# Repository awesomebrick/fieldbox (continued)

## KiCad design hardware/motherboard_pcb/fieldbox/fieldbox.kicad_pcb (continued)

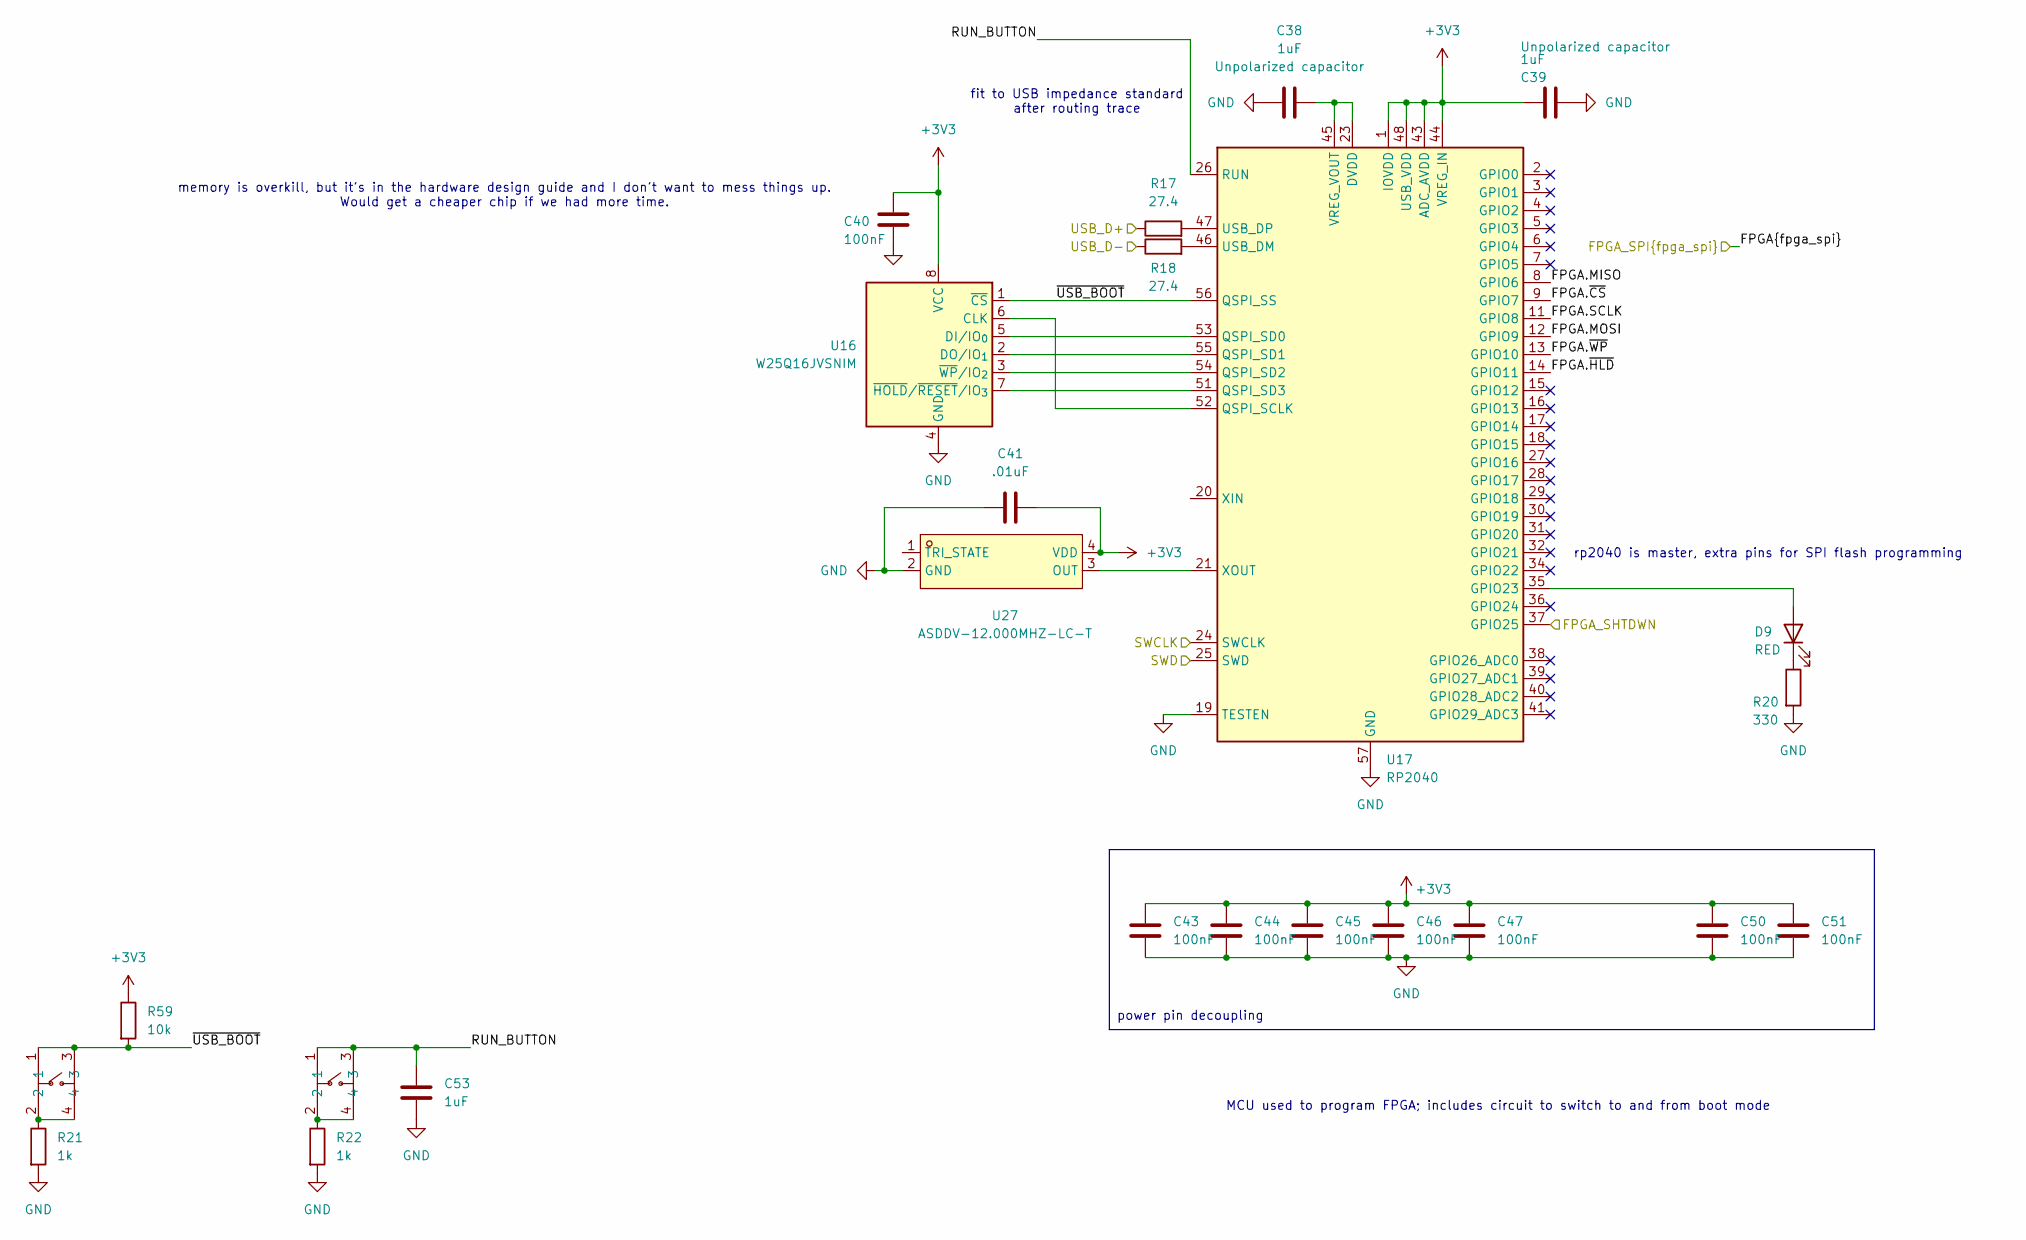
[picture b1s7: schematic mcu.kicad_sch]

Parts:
C38, C39, C53: 1uF; C_0603_1608Metric; Mouser # 791-0201X105M6R3CT
C40, C43, C44, C45, C46, C47, C50, C51: 100nF; C_0603_1608Metric; Mouser # KGM15AR71C104MM
C41: .01uF; C_0603_1608Metric; Mouser # 603-CC603ZRY5V8BB103
D9: RED; LED_0603_1608Metric; Mouser # 720-LSQ976.01-N1Q2-1
R17, R18: 27.4; R_0603_1608Metric; Mouser # 603-RC0603FR-0727R4L
R20: 330; R_0603_1608Metric; Mouser # 603-RC0603FR-10330RL
R21, R22: 1k; R_0603_1608Metric; Mouser # 660-RK73H1JTTDD1001F
R59: 10k; R_0603_1608Metric; Mouser # 652-CRT0603BY1002ELF
U16: W25Q16JVSNIM; SOIC-8_5.3x5.3mm_P1.27mm; Mouser # 454-W25Q16JVSNIM
U17: RP2040; QFN-56-1EP_7x7mm_P0.4mm_EP3.2x3.2mm; Mouser # 358-SC091413
U27: ASDDV-12.000MHZ-LC-T; OSC-SMD_4P-L2.5-W2.0-BL_ABRACON_ASTMLPD; Mouser # 815-ASDDV-1200MHZLCT; LCSC Part C1857773
b_up1, b_up2: TSD003A04126A02; SW-SMD_4P-L6.0-W6.0-P4.50-LS8.6; Mouser # NA; LCSC Part C2888573

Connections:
+3V3: C39.1, C40.1, C41.2, C43.1, C44.1, C45.1, C46.1, C47.1, C50.1, C51.1, R59.1, U16.8 (VCC), U17.1 (IOVDD), U17.10 (IOVDD), U17.22 (IOVDD), U17.33 (IOVDD), U17.42 (IOVDD), U17.43 (ADC_AVDD), U17.44 (VREG_IN), U17.48 (USB_VDD), U17.49 (IOVDD), U27.4 (VDD); also elsewhere on the board
/CV inputs/FPGA_SHTDWN: U17.37 (GPIO25); also elsewhere on the board
/FPGA/SPI_MASTER.MISO: U17.8 (GPIO6); also elsewhere on the board
/FPGA/SPI_MASTER.MOSI: U17.12 (GPIO9); also elsewhere on the board
/FPGA/SPI_MASTER.SCLK: U17.11 (GPIO8); also elsewhere on the board
/FPGA/SPI_MASTER.~CS: U17.9 (GPIO7); also elsewhere on the board
/FPGA/SPI_MASTER.~HLD: U17.14 (GPIO11); also elsewhere on the board
/FPGA/SPI_MASTER.~WP: U17.13 (GPIO10); also elsewhere on the board
/USB_D+: R17.1; also elsewhere on the board
/USB_D-: R18.1; also elsewhere on the board
/mcu/RUN_BUTTON: C53.1, U17.26 (RUN), b_up2.1, b_up2.3
/mcu/SWCLK: U17.24 (SWCLK); also elsewhere on the board
/mcu/SWD: U17.25 (SWD); also elsewhere on the board
/mcu/~USB_BOOT: R59.2, U16.1 (~CS), U17.56 (QSPI_SS), b_up1.1, b_up1.3
GND: C38.2, C39.2, C40.2, C41.1, C43.2, C44.2, C45.2, C46.2, C47.2, C50.2, C51.2, C53.2, R20.2, R21.2, R22.2, U16.4 (GND), U17.19 (TESTEN), U17.57 (GND), U27.2 (GND); also elsewhere on the board
unnamed: D9.2 (A), U17.35 (GPIO23)
unnamed: D9.1 (K), R20.1
unnamed: R21.1, b_up1.2, b_up1.4
unnamed: R22.1, b_up2.2, b_up2.4
unnamed: U16.6 (CLK), U17.52 (QSPI_SCLK)
unnamed: U16.5 (DI/IO_{0}), U17.53 (QSPI_SD0)
unnamed: U16.2 (DO/IO_{1}), U17.55 (QSPI_SD1)
unnamed: U16.7 (~HOLD/~RESET/IO_{3}), U17.51 (QSPI_SD3)
unnamed: U16.3 (~WP/IO_{2}), U17.54 (QSPI_SD2)
unnamed: R18.2, U17.46 (USB_DM)
unnamed: R17.2, U17.47 (USB_DP)
unnamed: C38.1, U17.23 (DVDD), U17.45 (VREG_VOUT), U17.50 (DVDD)
unnamed: U17.21 (XOUT), U27.3 (OUT)

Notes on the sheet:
power pin decoupling
MCU used to program FPGA; includes circuit to switch to and from boot mode
rp2040 is master, extra pins for SPI flash programming
fit to USB impedance standard after routing trace
memory is overkill, but it's in the hardware design guide and I don't want to mess things up. Would get a cheaper chip if we had more time.

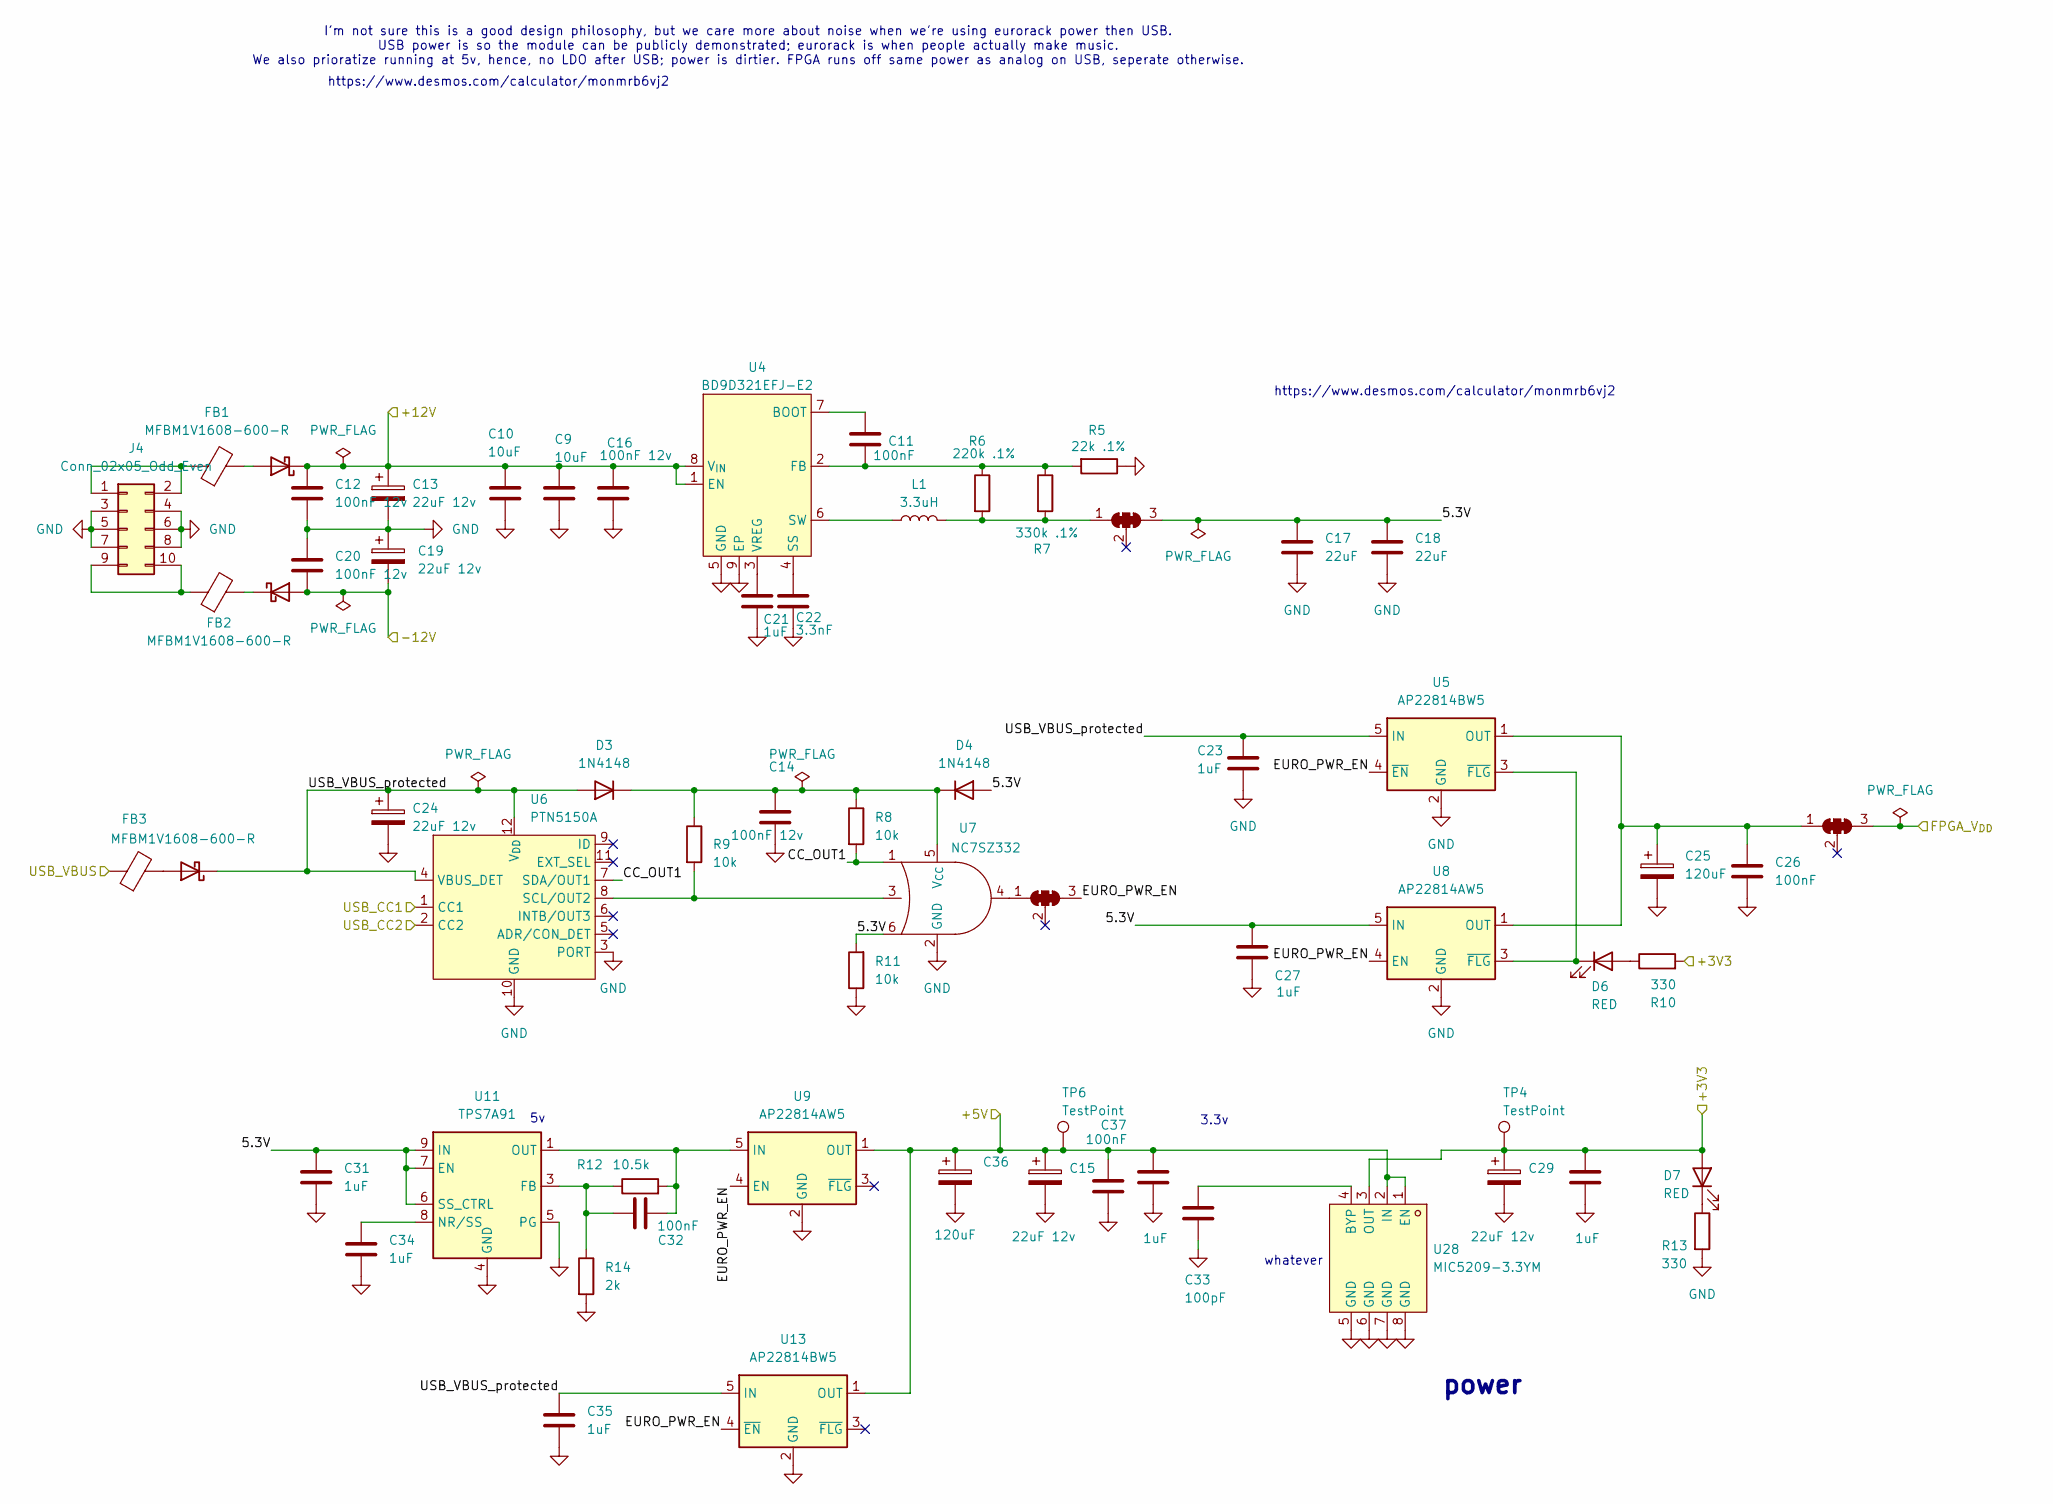
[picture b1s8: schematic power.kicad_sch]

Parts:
C9, C10: 10uF; CP_EIA-3216-18_Kemet-A; Mouser # 581-TAJA106K016R
C11, C26, C32, C37: 100nF; C_0603_1608Metric; Mouser # KGM15AR71C104MM
C12, C14, C16, C20: 100nF 12v; C_0603_1608Metric; Mouser # KGM15AR71C104MM
C13, C15, C19, C24, C29: 22uF 12v; CP_EIA-3528-21_Kemet-B; Mouser # 581-TAJB226K016TNJ
C17, C18: 22uF; C_0603_1608Metric; Mouser # 81-GRM188R60J226ME5J
C21, C23, C27, C28, C30, C31, C34, C35: 1uF; C_0603_1608Metric; Mouser # 791-0201X105M6R3CT
C22: 3.3nF; C_0603_1608Metric; Mouser # CL10B332KB8NFNC
C25, C36: 120uF; CP_EIA-3528-21_Kemet-B; Mouser # 581-TPSB107M006R0400
C33: 100pF; C_0603_1608Metric; Mouser # 603-CC603KRX7R8BB101
D1: SK34SMA-3G; D_SMA; Mouser # 637-SK34SMA-3G
D2, D5: SK34SMA-3G; D_SMA; mfr # SK34SMA-3G; Mouser # 637-SK34SMA-3G
D3, D4: 1N4148; D_SOD-323F; Mouser # 637-1N4148WS-AQ
D6, D7: RED; LED_0603_1608Metric; Mouser # 720-LSQ976.01-N1Q2-1
FB1, FB2, FB3: MFBM1V1608-600-R; L_0603_1608Metric; Mouser # 704-MFBM1V1608-600-R
J4: Conn_02x05_Odd_Even; IDC-Header_2x05_P2.54mm_Vertical; Mouser # 737-BHR-10-VUA
JP1, JP2, JP3: SolderJumper_3_Bridged123; SolderJumper-3_P2.0mm_Open_TrianglePad1.0x1.5mm
L1: 3.3uH; L_APV_ANR4012; Mouser # 963-NRS4012T3R3MDGJ
R5: 22k .1%; R_0603_1608Metric; Mouser # 754-RG1608P-223-B-T5
R6: 220k .1%; R_0603_1608Metric; Mouser # 754-RG1608P-224-BT5
R7: 330k .1%; R_0603_1608Metric; Mouser # 754-RG1608P-334-B-T5
R8, R9, R11: 10k; R_0603_1608Metric; Mouser # 652-CRT0603BY1002ELF
R10, R13: 330; R_0603_1608Metric; Mouser # 603-RC0603FR-10330RL
R12: 10.5k; R_0603_1608Metric; Mouser # 667-ERA-3AEB1052V
R14: 2k; R_0603_1608Metric; Mouser # 660-RN73H1JTD2001B25
TP4, TP6: TestPoint; TestPoint_Pad_2.0x2.0mm; Mouser # NA
U4: BD9D321EFJ-E2; HTSOP-8-1EP_3.9x4.9mm_P1.27mm_EP2.4x3.2mm; Mouser # 755-BD9D321EFJ-E2
U5, U13: AP22814BW5; SOT-23-5; Mouser # 621-AP22814BW5-7
U6: PTN5150A; Texas_X2QFN-12_1.6x1.6mm_P0.4mm; Mouser # 771-PTN5150AHXMP
U7: NC7SZ332; SOT-363_SC-70-6; Mouser # 512-NC7SZ332P6X
U8, U9: AP22814AW5; SOT-23-5; Mouser # 621-AP22814AW5-7
U11: TPS7A91; SON50P250X250X80-11N-D; Mouser # 595-TPS7A9101DSKR
U28: MIC5209-3.3YM; SOIC-8_L4.9-W3.9-P1.27-LS6.0-BL; Mouser # MIC5209-3.3YM

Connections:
+3V3: C29.1, C30.1, D7.2 (A), R10.2, TP4.1, U28.3 (OUT); also elsewhere on the board
+5V: C15.1, C28.1, C36.1, C37.1, TP6.1, U9.1 (OUT), U13.1 (OUT), U28.1 (EN), U28.2 (IN); also elsewhere on the board
+12V: C9.1, C10.1, C12.2, C13.1, C16.1, D1.1 (K), U4.1 (EN), U4.8 (V_{IN}); also elsewhere on the board
-12V: C19.2, C20.1, D2.2 (A); also elsewhere on the board
/FPGA/FPGA_VDD: JP2.3 (B); also elsewhere on the board
/USB_CC1: U6.1 (CC1); also elsewhere on the board
/USB_CC2: U6.2 (CC2); also elsewhere on the board
/USB_VBUS: FB3.1; also elsewhere on the board
/power/5.3V: C17.1, C18.1, C27.1, C31.1, D4.2 (A), JP1.3 (B), R11.2, U7.6, U8.5 (IN), U11.6 (SS_CTRL), U11.7 (EN), U11.9 (IN), U11.10 (IN)
/power/CC_OUT1: R8.2, U6.7 (SDA/OUT1), U7.1
/power/EURO_PWR_EN: JP3.3 (B), U5.4 (~EN), U8.4 (EN), U9.4 (EN), U13.4 (~EN)
/power/USB_VBUS_protected: C23.1, C24.1, C35.1, D3.2 (A), D5.1 (K), U5.5 (IN), U6.4 (VBUS_DET), U6.12 (V_{DD}), U13.5 (IN)
GND: C9.2, C10.2, C12.1, C13.2, C14.2, C15.2, C16.2, C17.2, C18.2, C19.1, C20.2, C21.2, C22.2, C23.2, C24.2, C25.2, C26.2, C27.2, C28.2, C29.2, C30.2, C31.2, C33.2, C34.2, C35.2, C36.2, C37.2, J4.3, J4.4, J4.5, J4.6, J4.7, J4.8, R5.1, R11.1, R13.2, R14.2, U4.5 (GND), U4.9 (EP), U5.2 (GND), U6.3 (PORT), U6.10 (GND), U7.2 (GND), U8.2 (GND), U9.2 (GND), U11.4 (GND), U11.5 (PG), U11.11 (GND), U13.2 (GND), U28.5 (GND), U28.6 (GND), U28.7 (GND), U28.8 (GND); also elsewhere on the board
unnamed: D1.2 (A), FB1.2
unnamed: D2.1 (K), FB2.2
unnamed: C14.1, D3.1 (K), D4.1 (K), R8.1, R9.1, U7.5 (V_{CC})
unnamed: D5.2 (A), FB3.2
unnamed: D6.2 (A), R10.1
unnamed: D6.1 (K), U5.3 (~FLG), U8.3 (~FLG)
unnamed: D7.1 (K), R13.1
unnamed: FB1.1, J4.1, J4.2
unnamed: FB2.1, J4.9, J4.10
unnamed: JP1.1 (A), L1.2, R6.2, R7.2
unnamed: C25.1, C26.1, JP2.1 (A), U5.1 (OUT), U8.1 (OUT)
unnamed: JP3.1 (A), U7.4
unnamed: C11.2, U4.7 (BOOT)
unnamed: C11.1, R5.2, R6.1, R7.1, U4.2 (FB)
unnamed: C22.1, U4.4 (SS)
unnamed: L1.1, U4.6 (SW)
unnamed: C21.1, U4.3 (VREG)
unnamed: R9.2, U6.8 (SCL/OUT2), U7.3
unnamed: C32.1, R12.2, U9.5 (IN), U11.1 (OUT), U11.2 (OUT)
unnamed: C32.2, R12.1, R14.1, U11.3 (FB)
unnamed: C34.1, U11.8 (NR/SS)
unnamed: C33.1, U28.4 (BYP)

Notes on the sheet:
3.3v
power
whatever
https://www.desmos.com/calculator/monmrb6vj2
I'm not sure this is a good design philosophy, but we care more about noise when we're using eurorack power then USB. USB power is so the module can be publicly demonstrated; eurorack is when people actually make music. We also prioratize running at 5v, hence, no LDO after USB; power is dirtier. FP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

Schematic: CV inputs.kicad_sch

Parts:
C54, C55, C56, C57: 100nF; C_0603_1608Metric; Mouser # KGM15AR71C104MM
C58: 10uF; CP_EIA-3216-18_Kemet-A; Mouser # 581-TAJA106K016R
C59: 100nF; C_0603_1608Metric; Mouser # KGM15AR71C104MM; not fitted
D10, D11, D12, D13, D15, D16, D18, D19: 1N4148; D_SOD-323F; Mouser # 637-1N4148WS-AQ
JP4: Jumper_2_Open; R_0603_1608Metric
R23, R24, R31, R32, R40, R41, R51, R52: 33k; R_0603_1608Metric; Mouser # CR0603-FX-3302ELF
R25: 10k .1%; R_0603_1608Metric; Mouser # 652-CRT0603BY1002ELF
R26, R28, R30, R33, R36, R37, R44, R45, R48, R53, R54, R55: 100k; R_0603_1608Metric; Mouser # CR0603-FX-1003ELF
R27, R29: 20k .1%; R_0603_1608Metric; Mouser # 708-RNCF0603BTC20K0
U1, U18, U21: TL074; TSSOP-14_4.4x5mm_P0.65mm; Mouser # 595-TL074HIPWR
U10: 74LVC1G32; SOT-353_SC-70-5; Mouser # 771-74LVC1G32GW-G
U20: MCP3462R; TSSOP-20_4.4x6.5mm_P0.65mm; Mouser # MCP3462R-E/ST

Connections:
+3V3: C54.2, C55.1, C56.2, C57.1, C58.1, C59.1, R27.1, U10.5 (VCC), U20.1 (AV_{DD}), U20.4 (RFIN+/OUT), U20.20 (DV_{DD}); also elsewhere on the board
+5V: D10.1 (K), D12.1 (K), D15.1 (K), D18.1 (K); also elsewhere on the board
+12V: U18.4 (V+), U21.4 (V+); also elsewhere on the board
-12V: U18.11 (V-), U21.11 (V-); also elsewhere on the board
/-5V_CUTOFF: D11.2 (A), D13.2 (A), D16.2 (A), D19.2 (A); also elsewhere on the board
/CV inputs/CV_ADC_MCLK: U20.18 (MCLK); also elsewhere on the board
/CV inputs/CV_REF: R23.1, R25.2, R31.1, R40.1, R51.1, U1.7
/CV inputs/FPGA_SHTDWN: U10.1; also elsewhere on the board
/CV inputs/RAW_SCALED_CV_1: JP4.2 (B); also elsewhere on the board
/CV inputs/SCALED_CV_1: JP4.1 (A), R24.2, U18.7, U20.5 (CH0)
/CV inputs/SCALED_CV_2: R32.2, U18.8, U20.6 (CH1)
/CV inputs/SCALED_CV_3: R41.2, U20.7 (CH2), U21.7
/CV inputs/SCALED_CV_4: R52.2, U20.8 (CH3), U21.8
/CV inputs/adc.MISO: U20.16 (SDO)
/CV inputs/adc.MOSI: U20.15 (SDI); also elsewhere on the board
/CV inputs/adc.SCLK: U20.14 (SCK); also elsewhere on the board
/CV inputs/adc.~IRQ: U20.17 (~IRQ/MDAT)
/CV inputs/adc.~SS: U10.2; also elsewhere on the board
/CV inputs/~SS: U10.4, U20.13 (~CS)
/EURORACK_CV_IN_1: R26.1; also elsewhere on the board
/EURORACK_CV_IN_2: R33.1; also elsewhere on the board
/EURORACK_CV_IN_3: R44.1; also elsewhere on the board
/EURORACK_CV_IN_4: R53.1; also elsewhere on the board
GND: C54.1, C55.2, C56.1, C57.2, C58.2, C59.2, R29.2, U1.5 (+), U10.3 (GND), U18.6 (-), U18.9 (-), U20.2 (A_{GND}), U20.3 (REFIN-), U20.19 (D_{GND}), U21.6 (-), U21.9 (-); also elsewhere on the board
unnamed: D10.2 (A), D11.1 (K), R26.2, U18.3 (+)
unnamed: D12.2 (A), D13.1 (K), R33.2, U18.12 (+)
unnamed: D15.2 (A), D16.1 (K), R44.2, U21.3 (+)
unnamed: D18.2 (A), D19.1 (K), R53.2, U21.12 (+)
unnamed: R28.1, R30.2, U18.1
unnamed: R36.1, R37.2, U18.14
unnamed: R45.1, R48.2, U21.1
unnamed: R54.1, R55.2, U21.14
unnamed: R25.1, R27.2, R29.1, U1.6 (-)
unnamed: R30.1, U18.2 (-)
unnamed: R23.2, R24.1, R28.2, U18.5 (+)
unnamed: R31.2, R32.1, R36.2, U18.10 (+)
unnamed: R37.1, U18.13 (-)
unnamed: R48.1, U21.2 (-)
unnamed: R40.2, R41.1, R45.2, U21.5 (+)
unnamed: R51.2, R52.1, R54.2, U21.10 (+)
unnamed: R55.1, U21.13 (-)

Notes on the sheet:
converts euro->CV ADC and contains CV ADC
<-- in case we don't get the external ADC working, we'll use the FPGA ADC
All these 10 ohm resistors are reccomended but probably useless in our case will remove if we're short on space
https://www.desmos.com/calculator/vk5jdnuxcy
CV inputs

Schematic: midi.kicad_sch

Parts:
D14, D17: 1N4148; D_SOD-323F; Mouser # 637-1N4148WS-AQ
R38, R47: 220; R_0603_1608Metric; Mouser # 652-CR0603FX-2200ELF
R39: 1k; R_0603_1608Metric; Mouser # 660-RK73H1JTTDD1001F
U19, U22: H11L1M; DIP-6_W7.62mm; Mouser # 512-H11L1M

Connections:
+3V3: R39.1, U19.6, U22.6; also elsewhere on the board
/FPGA/MIDI_IN: R39.2, U19.4, U22.4; also elsewhere on the board
/MIDI_IN_R: D17.2 (A), R38.1, U22.2; also elsewhere on the board
/MIDI_IN_S: D14.2 (A), R47.1, U19.2; also elsewhere on the board
GND: U19.5, U22.5; also elsewhere on the board
unnamed: D14.1 (K), R38.2, U19.1
unnamed: D17.1 (K), R47.2, U22.1

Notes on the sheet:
MIDI input

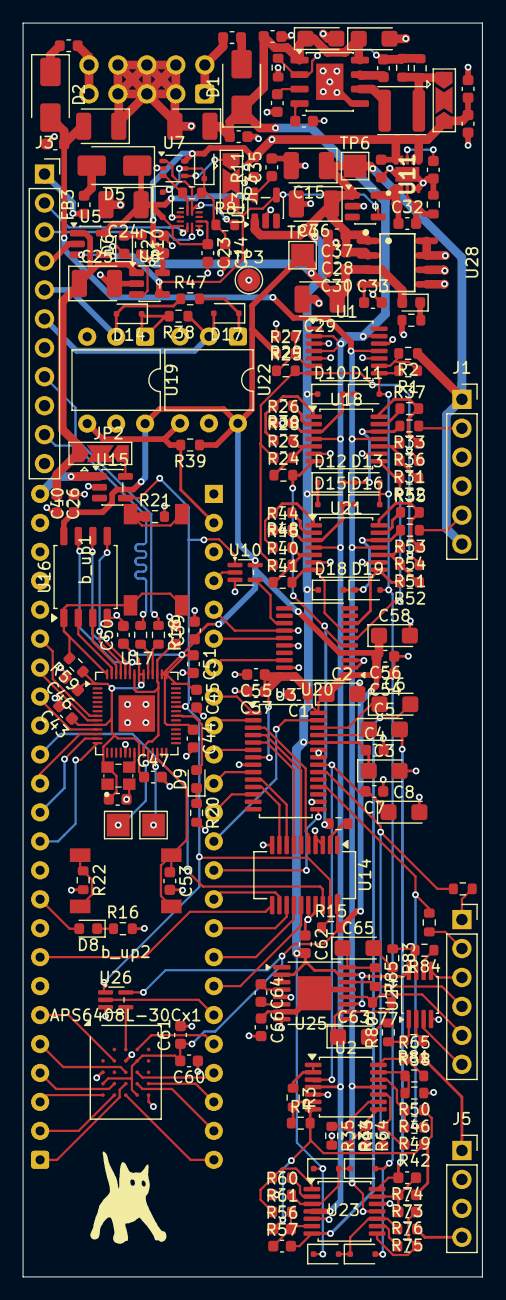
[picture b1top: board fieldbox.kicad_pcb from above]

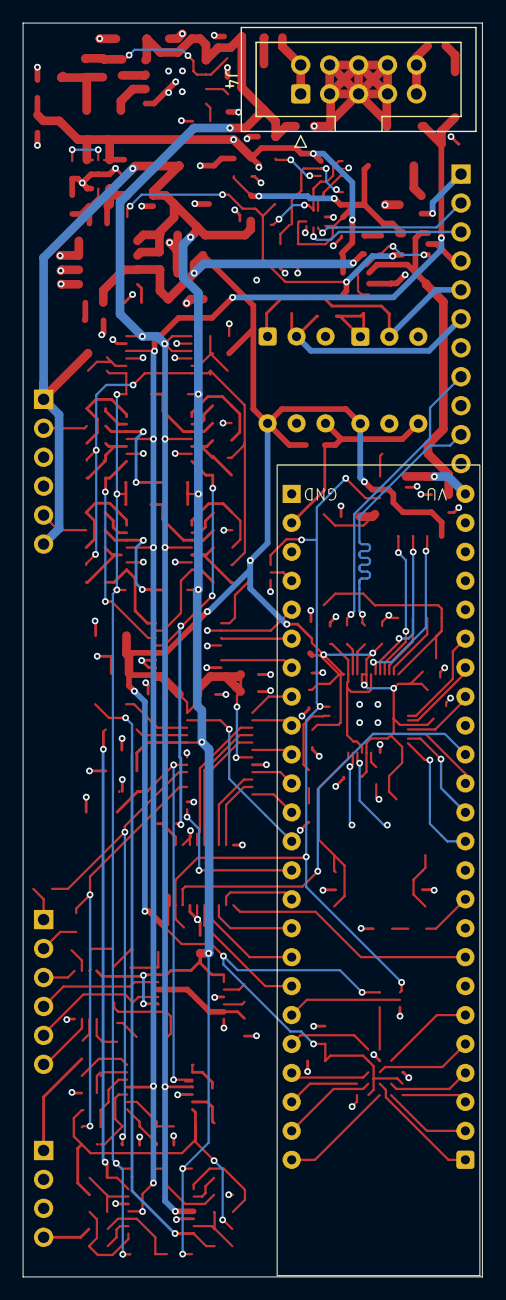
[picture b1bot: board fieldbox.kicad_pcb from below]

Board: 4 copper layers, 40.3 x 110.0 mm, 209 parts (2 on the bottom side), 179 nets.

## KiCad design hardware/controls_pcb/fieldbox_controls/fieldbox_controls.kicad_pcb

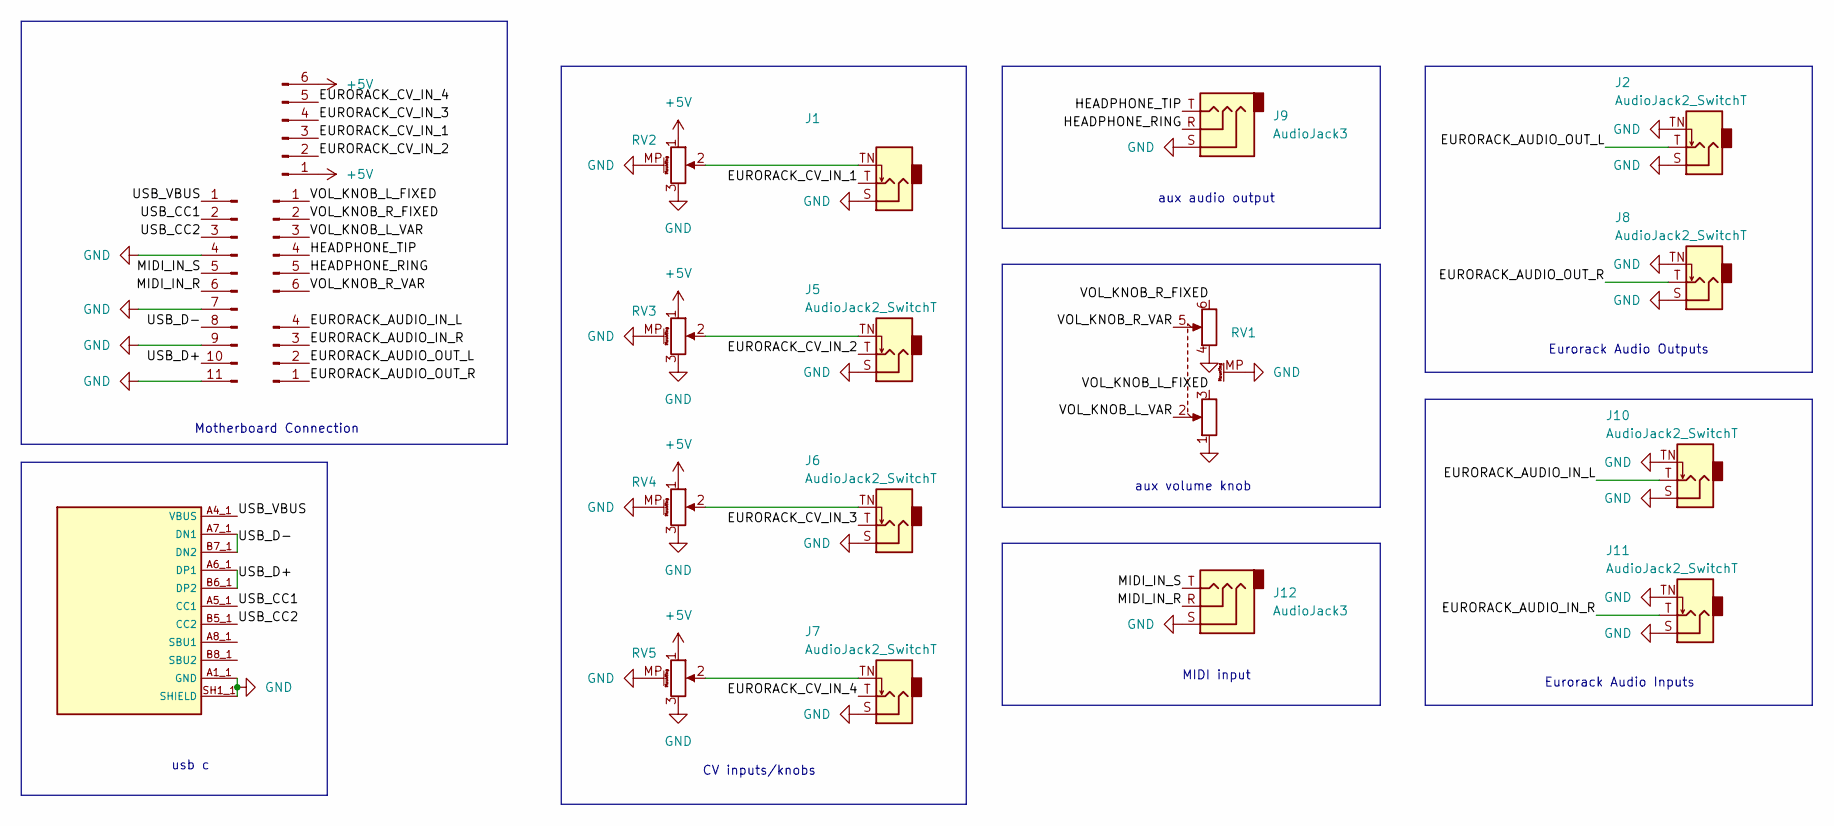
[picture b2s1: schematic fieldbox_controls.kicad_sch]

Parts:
J1, J2, J5, J6, J7, J8, J10, J11: AudioJack2_SwitchT; Jack_3.5mm_QingPu_WQP-PJ398SM_Vertical
J9, J12: AudioJack3; Jack_3.5mm_QingPu_WQP-PJ366ST_Vertical
J13: Conn_01x06_Socket; PinHeader_1x06_P2.54mm_Vertical
J14: Conn_01x04_Socket; PinHeader_1x06_P2.54mm_Vertical
J15: Conn_01x11_Socket; PinHeader_1x11_P2.54mm_Vertical
J16: Conn_01x04_Socket; PinHeader_1x04_P2.54mm_Vertical
RV1: R_Potentiometer_Dual_MountingPin; RK09L12D0A1W; Mouser # 688-RK09L12D0A1W
RV2, RV3, RV4, RV5: R_Potentiometer_MountingPin; RK09L114001E; Mouser # 688-RK09L114001T
U1: CUI_UJ20-C-V-C-3-SMT-TR; Mouser # 179-UJ20CVC3SMTTR

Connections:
+5V: J14.1, J14.6, RV2.1, RV3.1, RV4.1, RV5.1
/EURORACK_AUDIO_IN_L: J10.T, J16.4
/EURORACK_AUDIO_IN_R: J11.T, J16.3
/EURORACK_AUDIO_OUT_L: J2.T, J16.2
/EURORACK_AUDIO_OUT_R: J8.T, J16.1
/EURORACK_CV_IN_1: J1.T, J14.3
/EURORACK_CV_IN_2: J5.T, J14.2
/EURORACK_CV_IN_3: J6.T, J14.4
/EURORACK_CV_IN_4: J7.T, J14.5
/HEADPHONE_RING: J9.R, J13.5
/HEADPHONE_TIP: J9.T, J13.4
/MIDI_IN_R: J12.R, J15.6
/MIDI_IN_S: J12.T, J15.5
/USB_CC1: J15.2, U1.A5_1 (CC1), U1.A5_2 (CC1__1), U1.A5_3 (CC1__2), U1.A5_4 (CC1__3)
/USB_CC2: J15.3, U1.B5_1 (CC2), U1.B5_2 (CC2__1), U1.B5_3 (CC2__2), U1.B5_4 (CC2__3)
/USB_D+: J15.10, U1.A6_1 (DP1), U1.A6_2 (DP1__1), U1.A6_3 (DP1__2), U1.A6_4 (DP1__3), U1.B6_1 (DP2), U1.B6_2 (DP2__1), U1.B6_3 (DP2__2), U1.B6_4 (DP2__3)
/USB_D-: J15.8, U1.A7_1 (DN1), U1.A7_2 (DN1__1), U1.A7_3 (DN1__2), U1.A7_4 (DN1__3), U1.B7_1 (DN2), U1.B7_2 (DN2__1), U1.B7_3 (DN2__2), U1.B7_4 (DN2__3)
/USB_VBUS: J15.1, U1.A4_1 (VBUS), U1.A4_2 (VBUS__1), U1.A4_3 (VBUS__2), U1.A4_4 (VBUS__3), U1.A9_1 (VBUS__4), U1.A9_2 (VBUS__5), U1.A9_3 (VBUS__6), U1.A9_4 (VBUS__7), U1.B4_1 (VBUS__8), U1.B4_2 (VBUS__9), U1.B4_3 (VBUS__10), U1.B4_4 (VBUS__11), U1.B9_1 (VBUS__12), U1.B9_2 (VBUS__13), U1.B9_3 (VBUS__14), U1.B9_4 (VBUS__15)
/VOL_KNOB_L_FIXED: J13.1, RV1.3
/VOL_KNOB_L_VAR: J13.3, RV1.2
/VOL_KNOB_R_FIXED: J13.2, RV1.6
/VOL_KNOB_R_VAR: J13.6, RV1.5
GND: J1.S, J2.S, J2.TN, J5.S, J6.S, J7.S, J8.S, J8.TN, J9.S, J10.S, J10.TN, J11.S, J11.TN, J12.S, J15.4, J15.7, J15.9, J15.11, RV1.1, RV1.4, RV1.MP (MountPin), RV2.3, RV2.MP (MountPin), RV3.3, RV3.MP (MountPin), RV4.3, RV4.MP (MountPin), RV5.3, RV5.MP (MountPin), U1.A1_1 (GND), U1.A1_2 (GND__1), U1.A1_3 (GND__2), U1.A1_4 (GND__3), U1.A12_1 (GND__4), U1.A12_2 (GND__5), U1.A12_3 (GND__6), U1.A12_4 (GND__7), U1.B1_1 (GND__8), U1.B1_2 (GND__9), U1.B1_3 (GND__10), U1.B1_4 (GND__11), U1.B12_1 (GND__12), U1.B12_2 (GND__13), U1.B12_3 (GND__14), U1.B12_4 (GND__15), U1.SH1_1 (SHIELD), U1.SH1_2 (SHIELD__1), U1.SH1_3 (SHIELD__2), U1.SH1_4 (SHIELD__3), U1.SH2_1 (SHIELD__4), U1.SH2_2 (SHIELD__5), U1.SH2_3 (SHIELD__6), U1.SH2_4 (SHIELD__7), U1.SH3_1 (SHIELD__8), U1.SH3_2 (SHIELD__9), U1.SH3_3 (SHIELD__10), U1.SH3_4 (SHIELD__11), U1.SH4_1 (SHIELD__12), U1.SH4_2 (SHIELD__13), U1.SH4_3 (SHIELD__14), U1.SH4_4 (SHIELD__15)
unnamed: J1.TN, RV2.2
unnamed: J5.TN, RV3.2
unnamed: J6.TN, RV4.2
unnamed: J7.TN, RV5.2
unnamed: U1.A8_1 (SBU1), U1.A8_2 (SBU1__1), U1.A8_3 (SBU1__2), U1.A8_4 (SBU1__3)
unnamed: U1.B8_1 (SBU2), U1.B8_2 (SBU2__1), U1.B8_3 (SBU2__2), U1.B8_4 (SBU2__3)

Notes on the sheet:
MIDI input
CV inputs/knobs
Eurorack Audio Outputs
Eurorack Audio Inputs
usb c
Motherboard Connection
aux audio output
aux volume knob

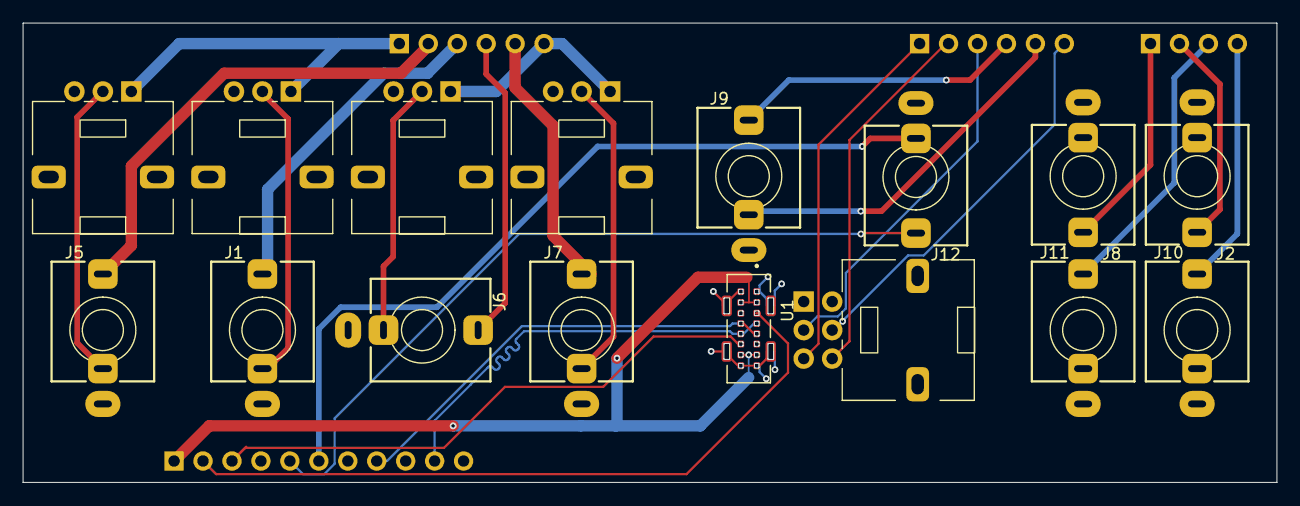
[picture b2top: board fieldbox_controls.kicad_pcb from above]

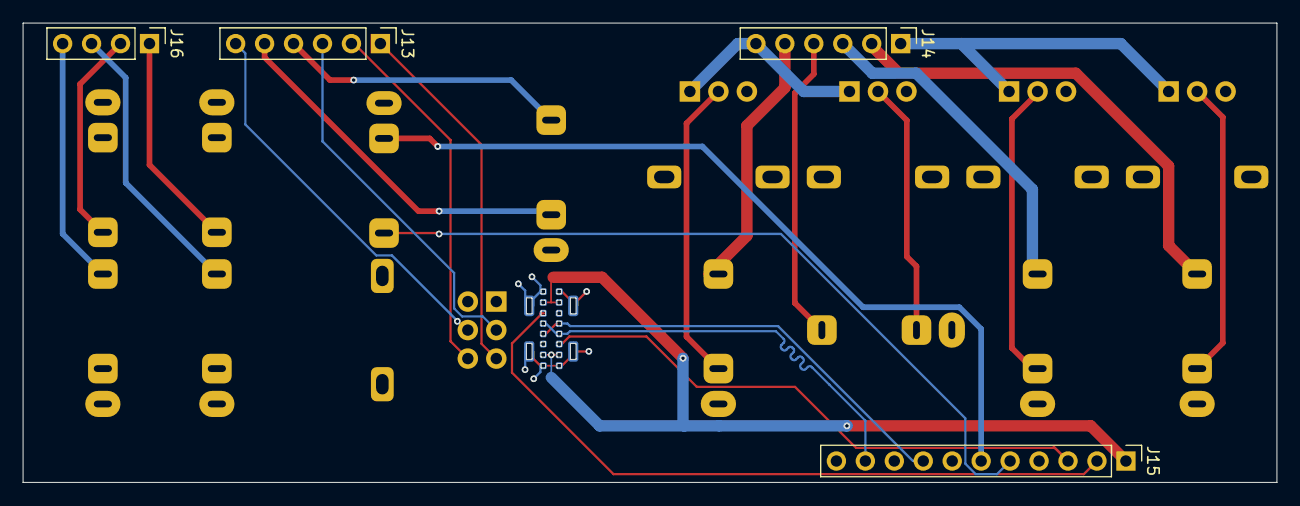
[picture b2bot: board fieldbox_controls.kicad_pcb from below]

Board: 4 copper layers, 110.0 x 40.3 mm, 20 parts (4 on the bottom side), 29 nets.

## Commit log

2025-11-19 inital folders and readme.
2025-12-19 test commit
2026-04-05 unorganized motherboard and controls board
